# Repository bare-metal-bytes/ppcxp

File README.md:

# 1.27 Pitch to 2.54 Pitch Converter Boards

Minimal, open-source, KiCad boards for converting dual-row 1.27 mm connectors to standard 2.54 mm headers.
Useful for prototyping, debugging, or breaking out fine-pitch connectors to breadboard-friendly spacing. Available variants: 40-pin, 20-pin, and 10-pin.

<p align="center">
  📟 <a href="https://www.pcbway.com/project/shareproject/Dual_row_40_pin_1_27_pitch_to_2_54_pitch_converter_board_1d84e70d.html">PCBWay Project</a>
</p>

This project was inspired by a need for quick, reliable adapter boards during embedded systems development (check out the [blog post](https://makeprogress.ee/blog/prototyping-in-an-hour-a-small-pcb)).

## License

This project is released under CERN Open Hardware Licence Version 2 - Permissive.

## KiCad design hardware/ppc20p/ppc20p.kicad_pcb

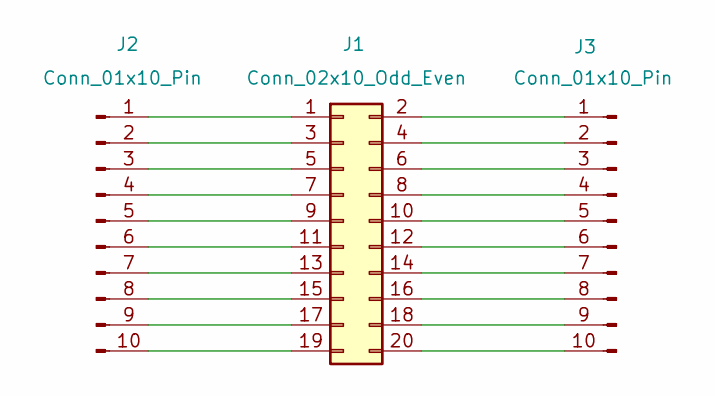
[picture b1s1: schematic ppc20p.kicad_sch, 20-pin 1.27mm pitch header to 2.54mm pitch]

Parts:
J1: Conn_02x10_Odd_Even; PinHeader_2x10_P1.27mm_Vertical
J2, J3: Conn_01x10_Pin; PinHeader_1x10_P2.54mm_Vertical

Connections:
unnamed: J1.1, J2.1
unnamed: J1.2, J3.1
unnamed: J1.3, J2.2
unnamed: J1.4, J3.2
unnamed: J1.5, J2.3
unnamed: J1.6, J3.3
unnamed: J1.7, J2.4
unnamed: J1.8, J3.4
unnamed: J1.9, J2.5
unnamed: J1.10, J3.5
unnamed: J1.11, J2.6
unnamed: J1.12, J3.6
unnamed: J1.13, J2.7
unnamed: J1.14, J3.7
unnamed: J1.15, J2.8
unnamed: J1.16, J3.8
unnamed: J1.17, J2.9
unnamed: J1.18, J3.9
unnamed: J1.19, J2.10
unnamed: J1.20, J3.10

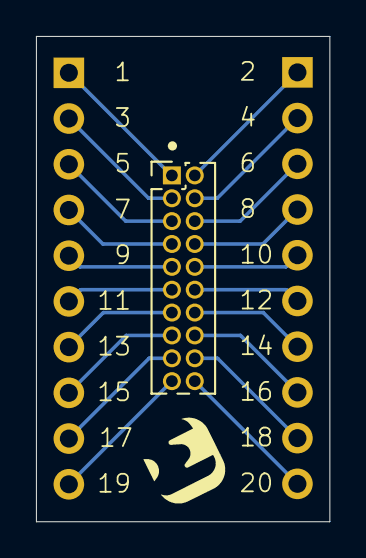
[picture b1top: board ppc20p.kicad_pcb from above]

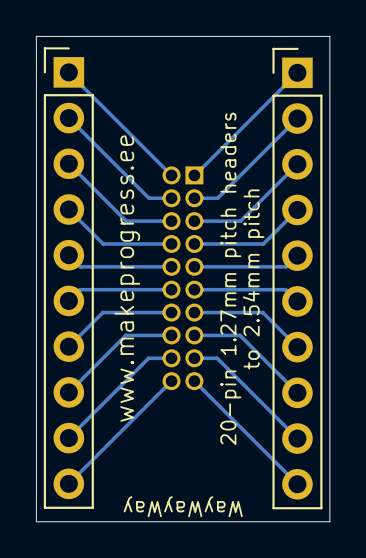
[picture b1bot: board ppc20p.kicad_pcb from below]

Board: 2 copper layers, 16.3 x 27.0 mm, 3 parts (2 on the bottom side), 20 nets.

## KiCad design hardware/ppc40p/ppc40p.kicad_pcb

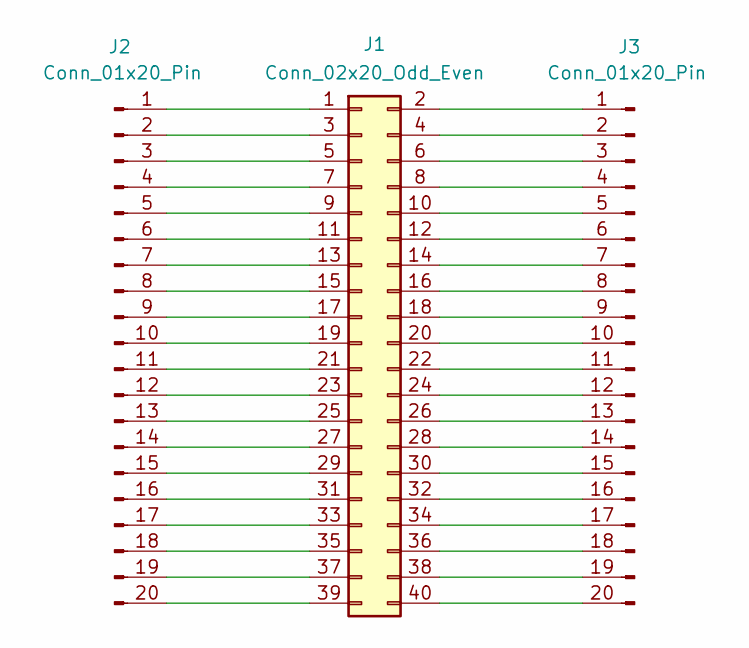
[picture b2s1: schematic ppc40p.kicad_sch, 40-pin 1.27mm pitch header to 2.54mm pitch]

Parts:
J1: Conn_02x20_Odd_Even; PinHeader_2x20_P1.27mm_Vertical
J2, J3: Conn_01x20_Pin; PinHeader_1x20_P2.54mm_Vertical

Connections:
unnamed: J1.1, J2.1
unnamed: J1.2, J3.1
unnamed: J1.3, J2.2
unnamed: J1.4, J3.2
unnamed: J1.5, J2.3
unnamed: J1.6, J3.3
unnamed: J1.7, J2.4
unnamed: J1.8, J3.4
unnamed: J1.9, J2.5
unnamed: J1.10, J3.5
unnamed: J1.11, J2.6
unnamed: J1.12, J3.6
unnamed: J1.13, J2.7
unnamed: J1.14, J3.7
unnamed: J1.15, J2.8
unnamed: J1.16, J3.8
unnamed: J1.17, J2.9
unnamed: J1.18, J3.9
unnamed: J1.19, J2.10
unnamed: J1.20, J3.10
unnamed: J1.21, J2.11
unnamed: J1.22, J3.11
unnamed: J1.23, J2.12
unnamed: J1.24, J3.12
unnamed: J1.25, J2.13
unnamed: J1.26, J3.13
unnamed: J1.27, J2.14
unnamed: J1.28, J3.14
unnamed: J1.29, J2.15
unnamed: J1.30, J3.15
unnamed: J1.31, J2.16
unnamed: J1.32, J3.16
unnamed: J1.33, J2.17
unnamed: J1.34, J3.17
unnamed: J1.35, J2.18
unnamed: J1.36, J3.18
unnamed: J1.37, J2.19
unnamed: J1.38, J3.19
unnamed: J1.39, J2.20
unnamed: J1.40, J3.20

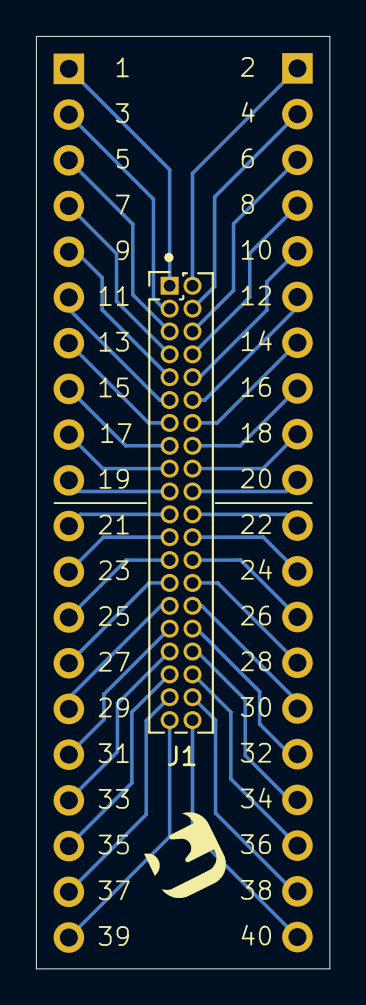
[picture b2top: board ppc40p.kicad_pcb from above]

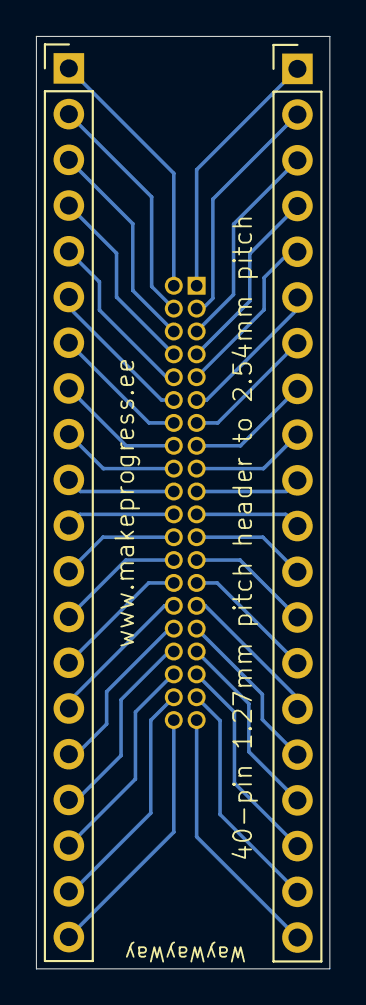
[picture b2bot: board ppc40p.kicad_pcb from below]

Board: 2 copper layers, 16.3 x 51.8 mm, 3 parts (2 on the bottom side), 40 nets.

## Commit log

2025-12-13 Initial commit with KiCad projects for 40, 20 and 10 pin converter boards
2025-12-18 Update readme with link to PCBWay project and link to blog post
